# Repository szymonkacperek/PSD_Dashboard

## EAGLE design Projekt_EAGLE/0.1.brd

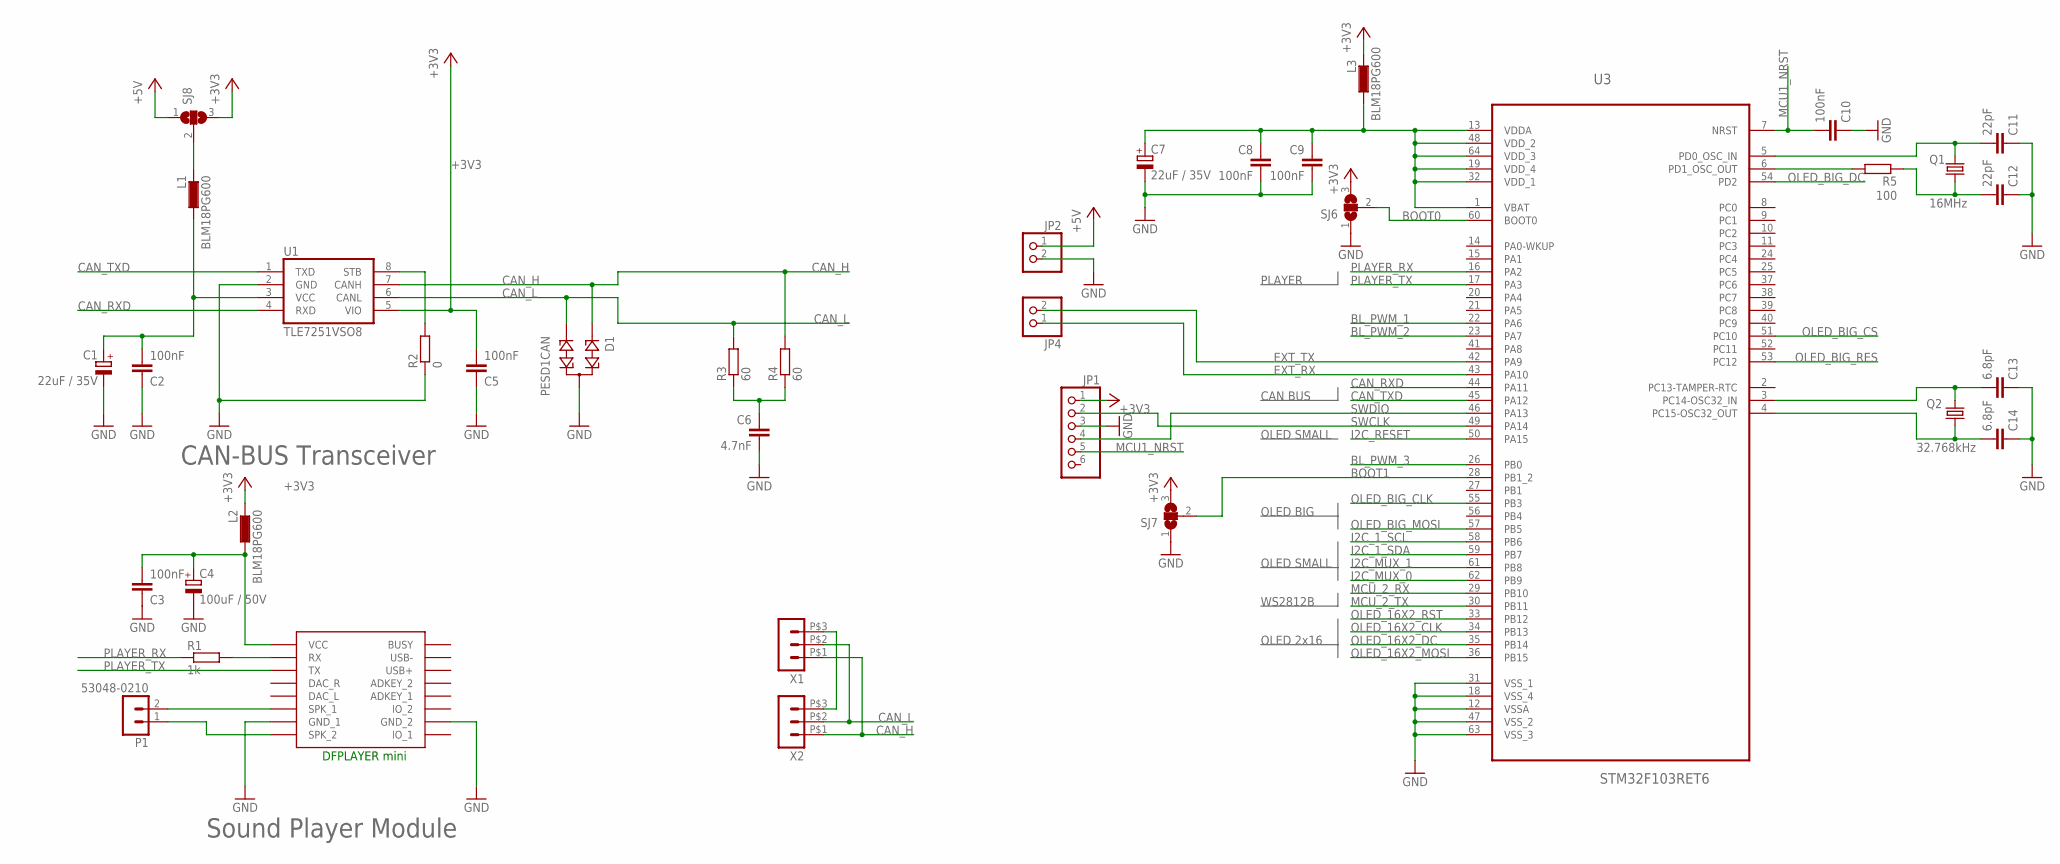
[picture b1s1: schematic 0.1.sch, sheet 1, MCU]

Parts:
C1, C7: 22uF / 35V; SMC_D
C2, C3, C5, C8, C9, C10: 100nF; C0805K
C4: 100uF / 50V; PANASONIC_F
C6: 4.7nF; C0805K
C11, C12: 22pF; C0805K
C13, C14: 6.8pF; C0805K
D1: PESD1CAN; SOT23
JP1: PINHD-1X6; 1X06
JP2, JP4: PINHD-1X2; 1X02
L1, L2, L3: BLM18PG600; L1608
P1: 53048-0210
Q1: 16MHz; SM49
Q2: 32.768kHz; SMD4_270
R1: 1k; R0805
R2: 0; R0805
R3, R4: 60; R0805
R5: 100; R0805
SJ6, SJ7, SJ8: SJ2W; SJ_2
U1: TLE7251VSO8; SO8
U2: DFPLAYER
U3: STM32F103RET6; QFP50P1200X1200X160-64N
X1, X2: HEADER_POS3_43650-0315; 43650-0315

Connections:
+3V3: C5.2, JP1.1, L2.2, L3.2, SJ6.3, SJ7.3, SJ8.3, U1.5 (VIO); also elsewhere on the board
+5V: JP2.1, SJ8.1; also elsewhere on the board
BL_PWM_1: U3.22 (PA6); also elsewhere on the board
BL_PWM_2: U3.23 (PA7); also elsewhere on the board
BL_PWM_3: U3.26 (PB0); also elsewhere on the board
BOOT0: SJ6.2, U3.60 (BOOT0)
BOOT1: SJ7.2, U3.28 (PB1_2)
CAN_H: D1.1, R4.2, U1.7 (CANH), X1.P$1 (1), X2.P$1 (1)
CAN_L: D1.2, R3.2, U1.6 (CANL), X1.P$2 (2), X2.P$2 (2)
CAN_RXD: U1.4 (RXD), U3.44 (PA11)
CAN_STB: R2.2, U1.8 (STB)
CAN_TXD: U1.1 (TXD), U3.45 (PA12)
EXT_RX: JP4.1, U3.43 (PA10)
EXT_TX: JP4.2, U3.42 (PA9)
GND: C1.-, C2.1, C3.1, C4.-, C5.1, C6.2, C7.-, C8.2, C9.2, C10.1, C11.1, C12.1, C13.1, C14.1, D1.3, JP1.3, JP2.2, R2.1, SJ6.1, SJ7.1, U1.2 (GND), U2.GND_1, U2.GND_2, U3.12 (VSSA), U3.18 (VSS_4), U3.31 (VSS_1), U3.47 (VSS_2), U3.63 (VSS_3); also elsewhere on the board
I2C_1_SCL: U3.58 (PB6); also elsewhere on the board
I2C_1_SDA: U3.59 (PB7); also elsewhere on the board
I2C_MUX_0: U3.62 (PB9); also elsewhere on the board
I2C_MUX_1: U3.61 (PB8); also elsewhere on the board
I2C_RESET: U3.50 (PA15); also elsewhere on the board
MCU1_NRST: C10.2, JP1.5, U3.7 (NRST)
MCU_2_RX: U3.29 (PB10); also elsewhere on the board
MCU_2_TX: U3.30 (PB11); also elsewhere on the board
unnamed: R5.2, U3.6 (PD1_OSC_OUT)
unnamed: R1.2, U2.RX
unnamed: C3.2, C4.+, L2.1, U2.VCC
unnamed: X1.P$3 (3), X2.P$3 (3)
unnamed: P1.1, U2.SPK2 (SPK_2)
unnamed: C6.1, R3.1, R4.1
unnamed: C7.+, C8.1, C9.1, L3.1, U3.1 (VBAT), U3.13 (VDDA), U3.19 (VDD_4), U3.32 (VDD_1), U3.48 (VDD_2), U3.64 (VDD_3)
unnamed: P1.2, U2.SPK1 (SPK_1)
unnamed: L1.2, SJ8.2
unnamed: C11.2, Q1.1, U3.5 (PD0_OSC_IN)
unnamed: C12.2, Q1.2, R5.1
unnamed: C13.2, Q2.4 (2), U3.3 (PC14-OSC32_IN)
unnamed: C14.2, Q2.1, U3.4 (PC15-OSC32_OUT)
unnamed: C1.+, C2.2, L1.1, U1.3 (VCC)
OLED_16X2_CLK: U3.34 (PB13); also elsewhere on the board
OLED_16X2_DC: U3.35 (PB14); also elsewhere on the board
OLED_16X2_MOSI: U3.36 (PB15); also elsewhere on the board
OLED_16X2_RST: U3.33 (PB12); also elsewhere on the board
OLED_BIG_CLK: U3.55 (PB3); also elsewhere on the board
OLED_BIG_CS: U3.51 (PC10); also elsewhere on the board
OLED_BIG_DC: U3.54 (PD2); also elsewhere on the board
OLED_BIG_MOSI: U3.57 (PB5); also elsewhere on the board
OLED_BIG_RES: U3.53 (PC12); also elsewhere on the board
PLAYER_RX: R1.1, U3.16 (PA2)
PLAYER_TX: U2.TX, U3.17 (PA3)
SWCLK: JP1.2, U3.49 (PA14)
SWDIO: JP1.4, U3.46 (PA13)

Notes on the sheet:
CAN-BUS Transceiver
Sound Player Module
OLED 2x16
OLED BIG
OLED SMALL
PLAYER
WS2812B
CAN BUS
DFPLAYER mini

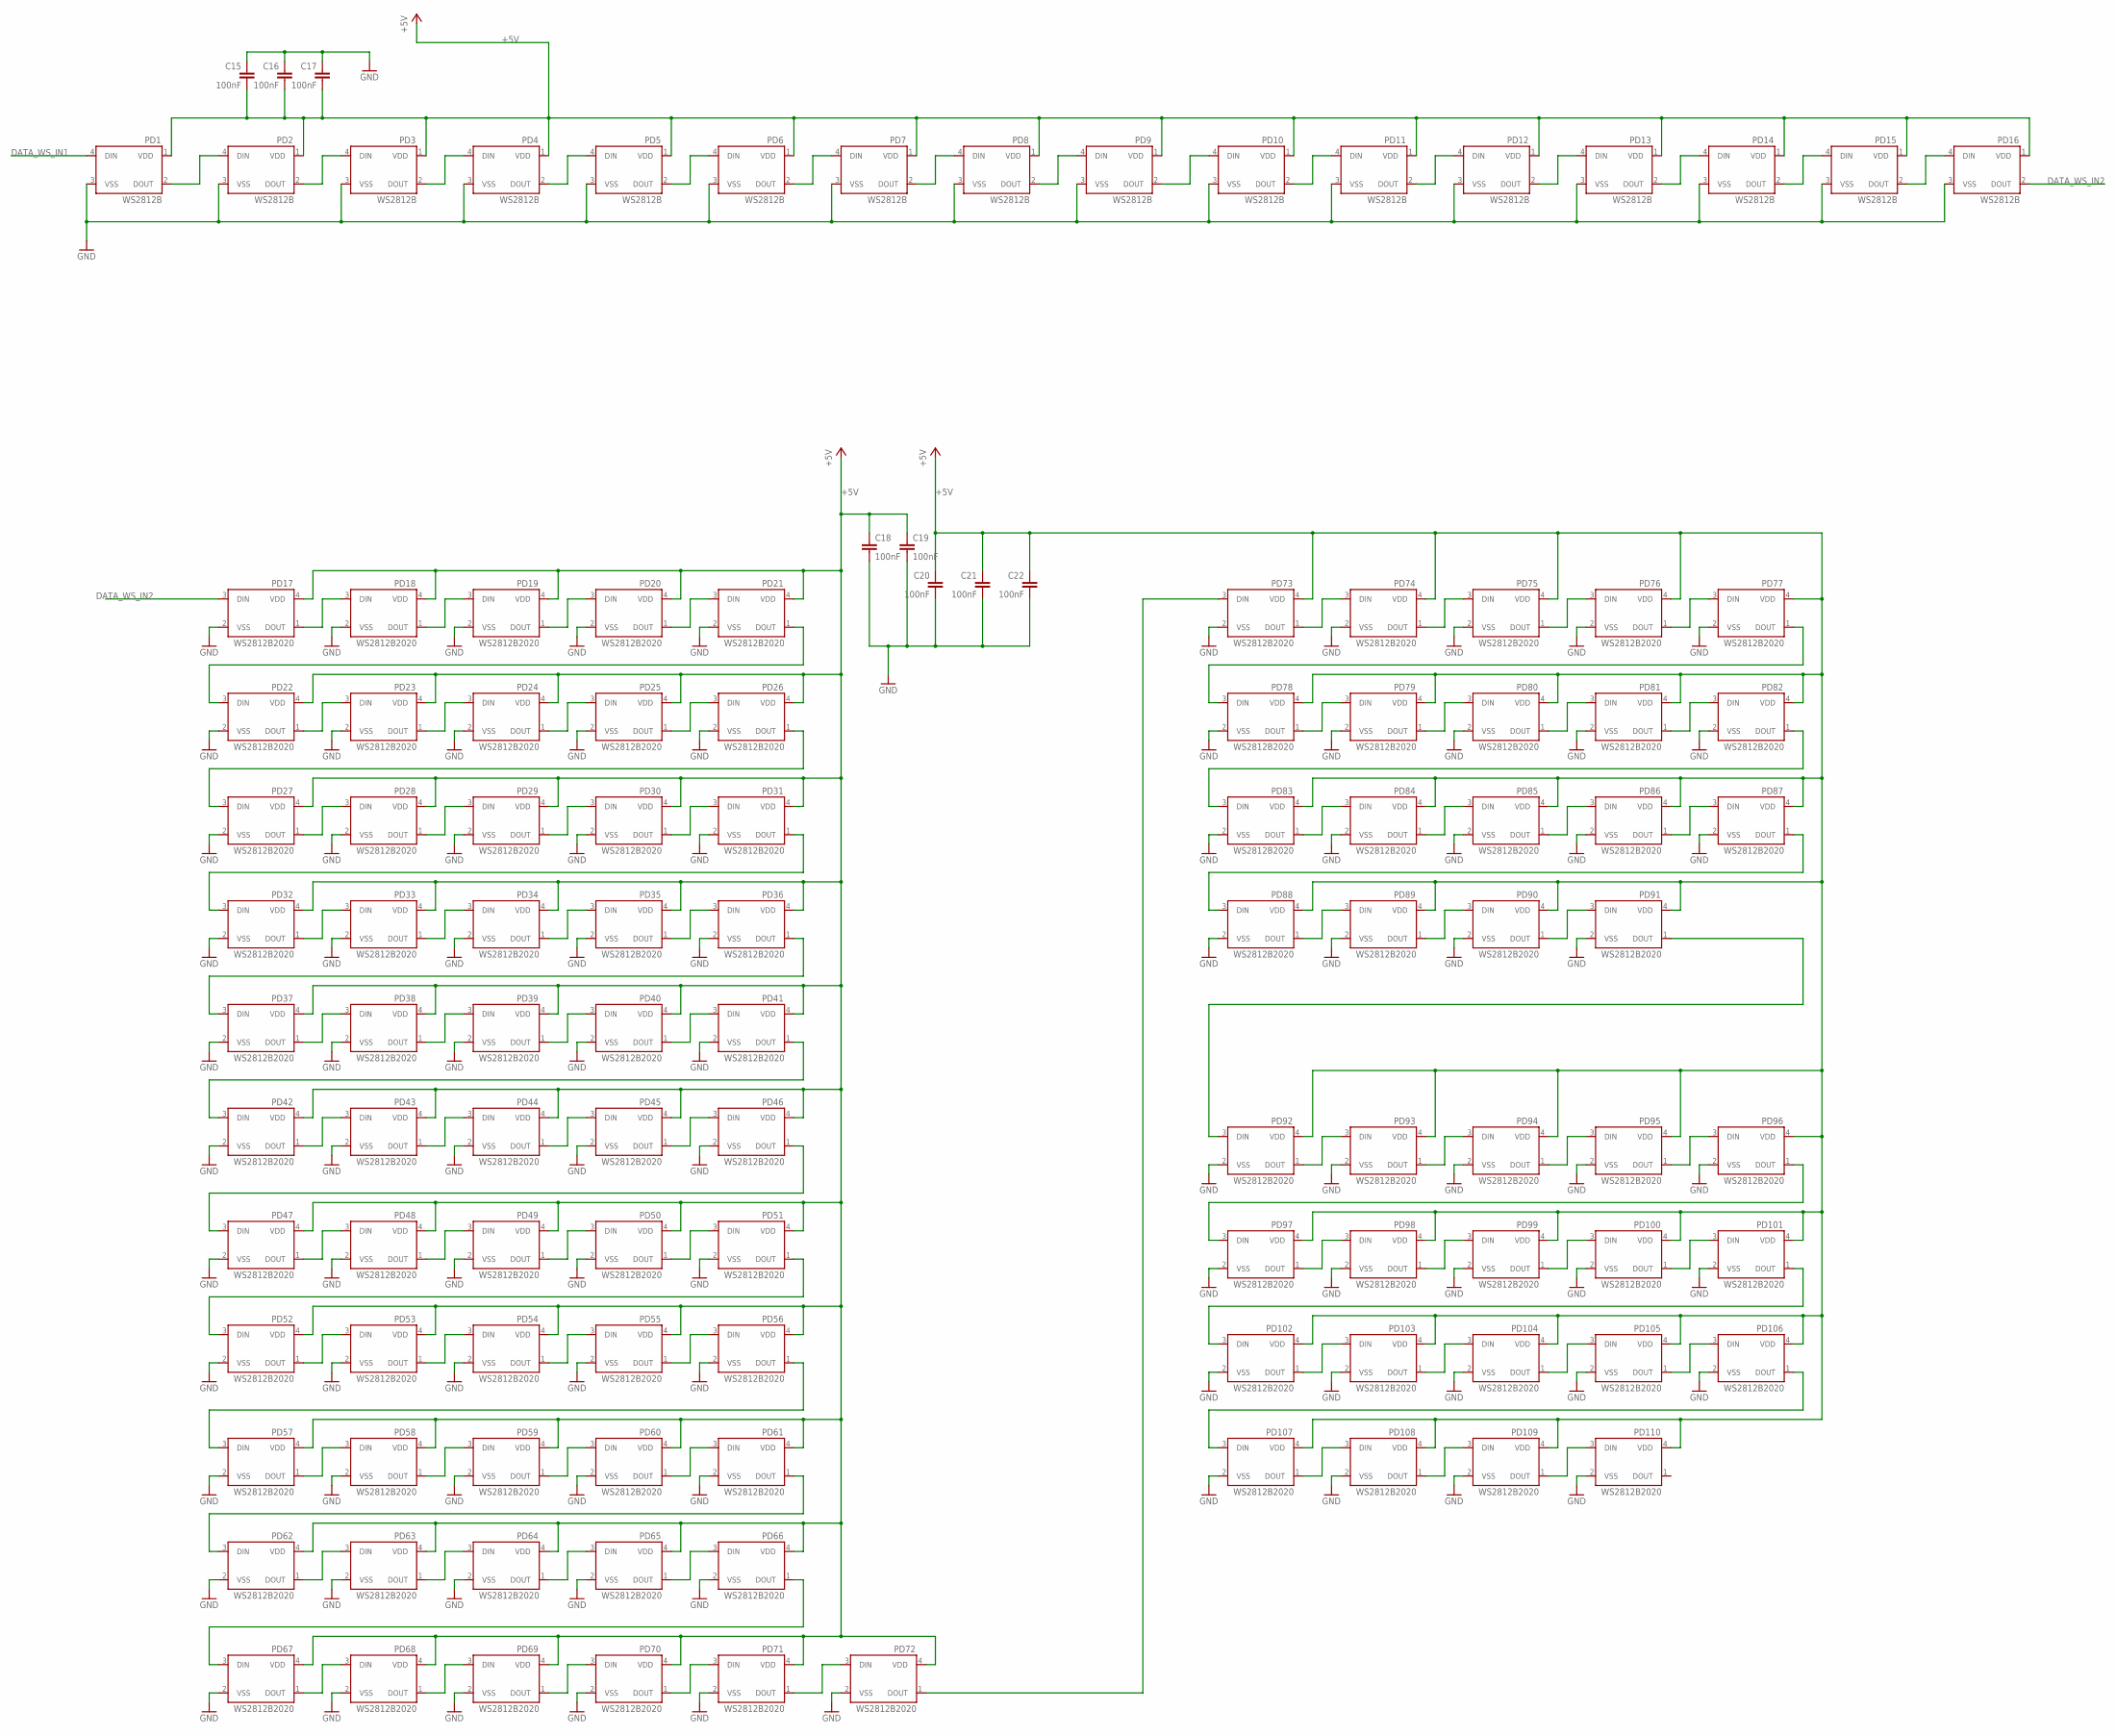
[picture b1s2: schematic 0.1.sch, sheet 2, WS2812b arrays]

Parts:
C15, C16, C17, C18, C19, C20, C21, C22: 100nF; C0805K
PD1, PD2, PD3, PD4, PD5, PD6, PD7, PD8, PD9, PD10, PD11, PD12, PD13, PD14, PD15, PD16: WS2812B; 5050
PD17, PD18, PD19, PD20, PD21, PD22, PD23, PD24, PD25, PD26, PD27, PD28, PD29, PD30, PD31, PD32, PD33, PD34, PD35, PD36, PD37, PD38, PD39, PD40, PD41, PD42, PD43, PD44, PD45, PD46, PD47, PD48, PD49, PD50, PD51, PD52, PD53, PD54, PD55, PD56, PD57, PD58, PD59, PD60, PD61, PD62, PD63, PD64, PD65, PD66, PD67, PD68, PD69, PD70, PD71, PD72, PD73, PD74, PD75, PD76, PD77, PD78, PD79, PD80, PD81, PD82, PD83, PD84, PD85, PD86, PD87, PD88, PD89, PD90, PD91, PD92, PD93, PD94, PD95, PD96, PD97, PD98, PD99, PD100, PD101, PD102, PD103, PD104, PD105, PD106, PD107, PD108, PD109, PD110: WS2812B2020; LED_WS2812-2020

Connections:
+5V: C15.2, C16.2, C17.2, C18.1, C19.1, C20.1, C21.1, C22.1, PD1.1 (VDD), PD2.1 (VDD), PD3.1 (VDD), PD4.1 (VDD), PD5.1 (VDD), PD6.1 (VDD), PD7.1 (VDD), PD8.1 (VDD), PD9.1 (VDD), PD10.1 (VDD), PD11.1 (VDD), PD12.1 (VDD), PD13.1 (VDD), PD14.1 (VDD), PD15.1 (VDD), PD16.1 (VDD), PD17.4 (VDD), PD18.4 (VDD), PD19.4 (VDD), PD20.4 (VDD), PD21.4 (VDD), PD22.4 (VDD), PD23.4 (VDD), PD24.4 (VDD), PD25.4 (VDD), PD26.4 (VDD), PD27.4 (VDD), PD28.4 (VDD), PD29.4 (VDD), PD30.4 (VDD), PD31.4 (VDD), PD32.4 (VDD), PD33.4 (VDD), PD34.4 (VDD), PD35.4 (VDD), PD36.4 (VDD), PD37.4 (VDD), PD38.4 (VDD), PD39.4 (VDD), PD40.4 (VDD), PD41.4 (VDD), PD42.4 (VDD), PD43.4 (VDD), PD44.4 (VDD), PD45.4 (VDD), PD46.4 (VDD), PD47.4 (VDD), PD48.4 (VDD), PD49.4 (VDD), PD50.4 (VDD), PD51.4 (VDD), PD52.4 (VDD), PD53.4 (VDD), PD54.4 (VDD), PD55.4 (VDD), PD56.4 (VDD), PD57.4 (VDD), PD58.4 (VDD), PD59.4 (VDD), PD60.4 (VDD), PD61.4 (VDD), PD62.4 (VDD), PD63.4 (VDD), PD64.4 (VDD), PD65.4 (VDD), PD66.4 (VDD), PD67.4 (VDD), PD68.4 (VDD), PD69.4 (VDD), PD70.4 (VDD), PD71.4 (VDD), PD72.4 (VDD), PD73.4 (VDD), PD74.4 (VDD), PD75.4 (VDD), PD76.4 (VDD), PD77.4 (VDD), PD78.4 (VDD), PD79.4 (VDD), PD80.4 (VDD), PD81.4 (VDD), PD82.4 (VDD), PD83.4 (VDD), PD84.4 (VDD), PD85.4 (VDD), PD86.4 (VDD), PD87.4 (VDD), PD88.4 (VDD), PD89.4 (VDD), PD90.4 (VDD), PD91.4 (VDD), PD92.4 (VDD), PD93.4 (VDD), PD94.4 (VDD), PD95.4 (VDD), PD96.4 (VDD), PD97.4 (VDD), PD98.4 (VDD), PD99.4 (VDD), PD100.4 (VDD), PD101.4 (VDD), PD102.4 (VDD), PD103.4 (VDD), PD104.4 (VDD), PD105.4 (VDD), PD106.4 (VDD), PD107.4 (VDD), PD108.4 (VDD), PD109.4 (VDD), PD110.4 (VDD); also elsewhere on the board
DATA_WS_IN1: PD1.4 (DIN); also elsewhere on the board
DATA_WS_IN2: PD16.2 (DOUT), PD17.3 (DIN)
DATA_WS_IN3: PD72.1 (DOUT), PD73.3 (DIN)
GND: C15.1, C16.1, C17.1, C18.2, C19.2, C20.2, C21.2, C22.2, PD1.3 (VSS), PD2.3 (VSS), PD3.3 (VSS), PD4.3 (VSS), PD5.3 (VSS), PD6.3 (VSS), PD7.3 (VSS), PD8.3 (VSS), PD9.3 (VSS), PD10.3 (VSS), PD11.3 (VSS), PD12.3 (VSS), PD13.3 (VSS), PD14.3 (VSS), PD15.3 (VSS), PD16.3 (VSS), PD17.2 (VSS), PD18.2 (VSS), PD19.2 (VSS), PD20.2 (VSS), PD21.2 (VSS), PD22.2 (VSS), PD23.2 (VSS), PD24.2 (VSS), PD25.2 (VSS), PD26.2 (VSS), PD27.2 (VSS), PD28.2 (VSS), PD29.2 (VSS), PD30.2 (VSS), PD31.2 (VSS), PD32.2 (VSS), PD33.2 (VSS), PD34.2 (VSS), PD35.2 (VSS), PD36.2 (VSS), PD37.2 (VSS), PD38.2 (VSS), PD39.2 (VSS), PD40.2 (VSS), PD41.2 (VSS), PD42.2 (VSS), PD43.2 (VSS), PD44.2 (VSS), PD45.2 (VSS), PD46.2 (VSS), PD47.2 (VSS), PD48.2 (VSS), PD49.2 (VSS), PD50.2 (VSS), PD51.2 (VSS), PD52.2 (VSS), PD53.2 (VSS), PD54.2 (VSS), PD55.2 (VSS), PD56.2 (VSS), PD57.2 (VSS), PD58.2 (VSS), PD59.2 (VSS), PD60.2 (VSS), PD61.2 (VSS), PD62.2 (VSS), PD63.2 (VSS), PD64.2 (VSS), PD65.2 (VSS), PD66.2 (VSS), PD67.2 (VSS), PD68.2 (VSS), PD69.2 (VSS), PD70.2 (VSS), PD71.2 (VSS), PD72.2 (VSS), PD73.2 (VSS), PD74.2 (VSS), PD75.2 (VSS), PD76.2 (VSS), PD77.2 (VSS), PD78.2 (VSS), PD79.2 (VSS), PD80.2 (VSS), PD81.2 (VSS), PD82.2 (VSS), PD83.2 (VSS), PD84.2 (VSS), PD85.2 (VSS), PD86.2 (VSS), PD87.2 (VSS), PD88.2 (VSS), PD89.2 (VSS), PD90.2 (VSS), PD91.2 (VSS), PD92.2 (VSS), PD93.2 (VSS), PD94.2 (VSS), PD95.2 (VSS), PD96.2 (VSS), PD97.2 (VSS), PD98.2 (VSS), PD99.2 (VSS), PD100.2 (VSS), PD101.2 (VSS), PD102.2 (VSS), PD103.2 (VSS), PD104.2 (VSS), PD105.2 (VSS), PD106.2 (VSS), PD107.2 (VSS), PD108.2 (VSS), PD109.2 (VSS), PD110.2 (VSS); also elsewhere on the board
unnamed: PD1.2 (DOUT), PD2.4 (DIN)
unnamed: PD2.2 (DOUT), PD3.4 (DIN)
unnamed: PD3.2 (DOUT), PD4.4 (DIN)
unnamed: PD4.2 (DOUT), PD5.4 (DIN)
unnamed: PD5.2 (DOUT), PD6.4 (DIN)
unnamed: PD6.2 (DOUT), PD7.4 (DIN)
unnamed: PD7.2 (DOUT), PD8.4 (DIN)
unnamed: PD9.2 (DOUT), PD10.4 (DIN)
unnamed: PD10.2 (DOUT), PD11.4 (DIN)
unnamed: PD11.2 (DOUT), PD12.4 (DIN)
unnamed: PD12.2 (DOUT), PD13.4 (DIN)
unnamed: PD13.2 (DOUT), PD14.4 (DIN)
unnamed: PD14.2 (DOUT), PD15.4 (DIN)
unnamed: PD15.2 (DOUT), PD16.4 (DIN)
unnamed: PD8.2 (DOUT), PD9.4 (DIN)
unnamed: PD21.1 (DOUT), PD22.3 (DIN)
unnamed: PD17.1 (DOUT), PD18.3 (DIN)
unnamed: PD18.1 (DOUT), PD19.3 (DIN)
unnamed: PD19.1 (DOUT), PD20.3 (DIN)
unnamed: PD20.1 (DOUT), PD21.3 (DIN)
unnamed: PD22.1 (DOUT), PD23.3 (DIN)
unnamed: PD23.1 (DOUT), PD24.3 (DIN)
unnamed: PD24.1 (DOUT), PD25.3 (DIN)
unnamed: PD25.1 (DOUT), PD26.3 (DIN)
unnamed: PD26.1 (DOUT), PD27.3 (DIN)
unnamed: PD27.1 (DOUT), PD28.3 (DIN)
unnamed: PD28.1 (DOUT), PD29.3 (DIN)
unnamed: PD29.1 (DOUT), PD30.3 (DIN)
unnamed: PD30.1 (DOUT), PD31.3 (DIN)
unnamed: PD31.1 (DOUT), PD32.3 (DIN)
unnamed: PD32.1 (DOUT), PD33.3 (DIN)
unnamed: PD33.1 (DOUT), PD34.3 (DIN)
unnamed: PD34.1 (DOUT), PD35.3 (DIN)
unnamed: PD35.1 (DOUT), PD36.3 (DIN)
unnamed: PD36.1 (DOUT), PD37.3 (DIN)
unnamed: PD37.1 (DOUT), PD38.3 (DIN)
unnamed: PD38.1 (DOUT), PD39.3 (DIN)
unnamed: PD39.1 (DOUT), PD40.3 (DIN)
unnamed: PD40.1 (DOUT), PD41.3 (DIN)
unnamed: PD41.1 (DOUT), PD42.3 (DIN)
unnamed: PD42.1 (DOUT), PD43.3 (DIN)
unnamed: PD43.1 (DOUT), PD44.3 (DIN)
unnamed: PD44.1 (DOUT), PD45.3 (DIN)
unnamed: PD45.1 (DOUT), PD46.3 (DIN)
unnamed: PD46.1 (DOUT), PD47.3 (DIN)
unnamed: PD47.1 (DOUT), PD48.3 (DIN)
unnamed: PD48.1 (DOUT), PD49.3 (DIN)
unnamed: PD49.1 (DOUT), PD50.3 (DIN)
unnamed: PD50.1 (DOUT), PD51.3 (DIN)
unnamed: PD51.1 (DOUT), PD52.3 (DIN)
unnamed: PD52.1 (DOUT), PD53.3 (DIN)
unnamed: PD53.1 (DOUT), PD54.3 (DIN)
unnamed: PD54.1 (DOUT), PD55.3 (DIN)
unnamed: PD55.1 (DOUT), PD56.3 (DIN)
unnamed: PD56.1 (DOUT), PD57.3 (DIN)
unnamed: PD57.1 (DOUT), PD58.3 (DIN)
unnamed: PD58.1 (DOUT), PD59.3 (DIN)
unnamed: PD59.1 (DOUT), PD60.3 (DIN)
unnamed: PD60.1 (DOUT), PD61.3 (DIN)
unnamed: PD61.1 (DOUT), PD62.3 (DIN)
unnamed: PD62.1 (DOUT), PD63.3 (DIN)
unnamed: PD63.1 (DOUT), PD64.3 (DIN)
unnamed: PD64.1 (DOUT), PD65.3 (DIN)
unnamed: PD65.1 (DOUT), PD66.3 (DIN)
unnamed: PD66.1 (DOUT), PD67.3 (DIN)
unnamed: PD92.1 (DOUT), PD93.3 (DIN)
unnamed: PD67.1 (DOUT), PD68.3 (DIN)
unnamed: PD68.1 (DOUT), PD69.3 (DIN)
unnamed: PD69.1 (DOUT), PD70.3 (DIN)
unnamed: PD70.1 (DOUT), PD71.3 (DIN)
unnamed: PD71.1 (DOUT), PD72.3 (DIN)
unnamed: PD93.1 (DOUT), PD94.3 (DIN)
unnamed: PD94.1 (DOUT), PD95.3 (DIN)
unnamed: PD95.1 (DOUT), PD96.3 (DIN)
unnamed: PD73.1 (DOUT), PD74.3 (DIN)
unnamed: PD74.1 (DOUT), PD75.3 (DIN)
unnamed: PD75.1 (DOUT), PD76.3 (DIN)
unnamed: PD76.1 (DOUT), PD77.3 (DIN)
unnamed: PD77.1 (DOUT), PD78.3 (DIN)
unnamed: PD78.1 (DOUT), PD79.3 (DIN)
unnamed: PD79.1 (DOUT), PD80.3 (DIN)
unnamed: PD80.1 (DOUT), PD81.3 (DIN)
unnamed: PD81.1 (DOUT), PD82.3 (DIN)
unnamed: PD82.1 (DOUT), PD83.3 (DIN)
unnamed: PD83.1 (DOUT), PD84.3 (DIN)
unnamed: PD84.1 (DOUT), PD85.3 (DIN)
unnamed: PD85.1 (DOUT), PD86.3 (DIN)
unnamed: PD86.1 (DOUT), PD87.3 (DIN)
unnamed: PD87.1 (DOUT), PD88.3 (DIN)
unnamed: PD88.1 (DOUT), PD89.3 (DIN)
unnamed: PD89.1 (DOUT), PD90.3 (DIN)
unnamed: PD90.1 (DOUT), PD91.3 (DIN)
unnamed: PD91.1 (DOUT), PD92.3 (DIN)
unnamed: PD96.1 (DOUT), PD97.3 (DIN)
unnamed: PD97.1 (DOUT), PD98.3 (DIN)
unnamed: PD98.1 (DOUT), PD99.3 (DIN)
unnamed: PD99.1 (DOUT), PD100.3 (DIN)
unnamed: PD100.1 (DOUT), PD101.3 (DIN)
unnamed: PD101.1 (DOUT), PD102.3 (DIN)
unnamed: PD102.1 (DOUT), PD103.3 (DIN)
unnamed: PD103.1 (DOUT), PD104.3 (DIN)
unnamed: PD104.1 (DOUT), PD105.3 (DIN)
unnamed: PD105.1 (DOUT), PD106.3 (DIN)
unnamed: PD106.1 (DOUT), PD107.3 (DIN)
unnamed: PD107.1 (DOUT), PD108.3 (DIN)
unnamed: PD108.1 (DOUT), PD109.3 (DIN)
unnamed: PD109.1 (DOUT), PD110.3 (DIN)

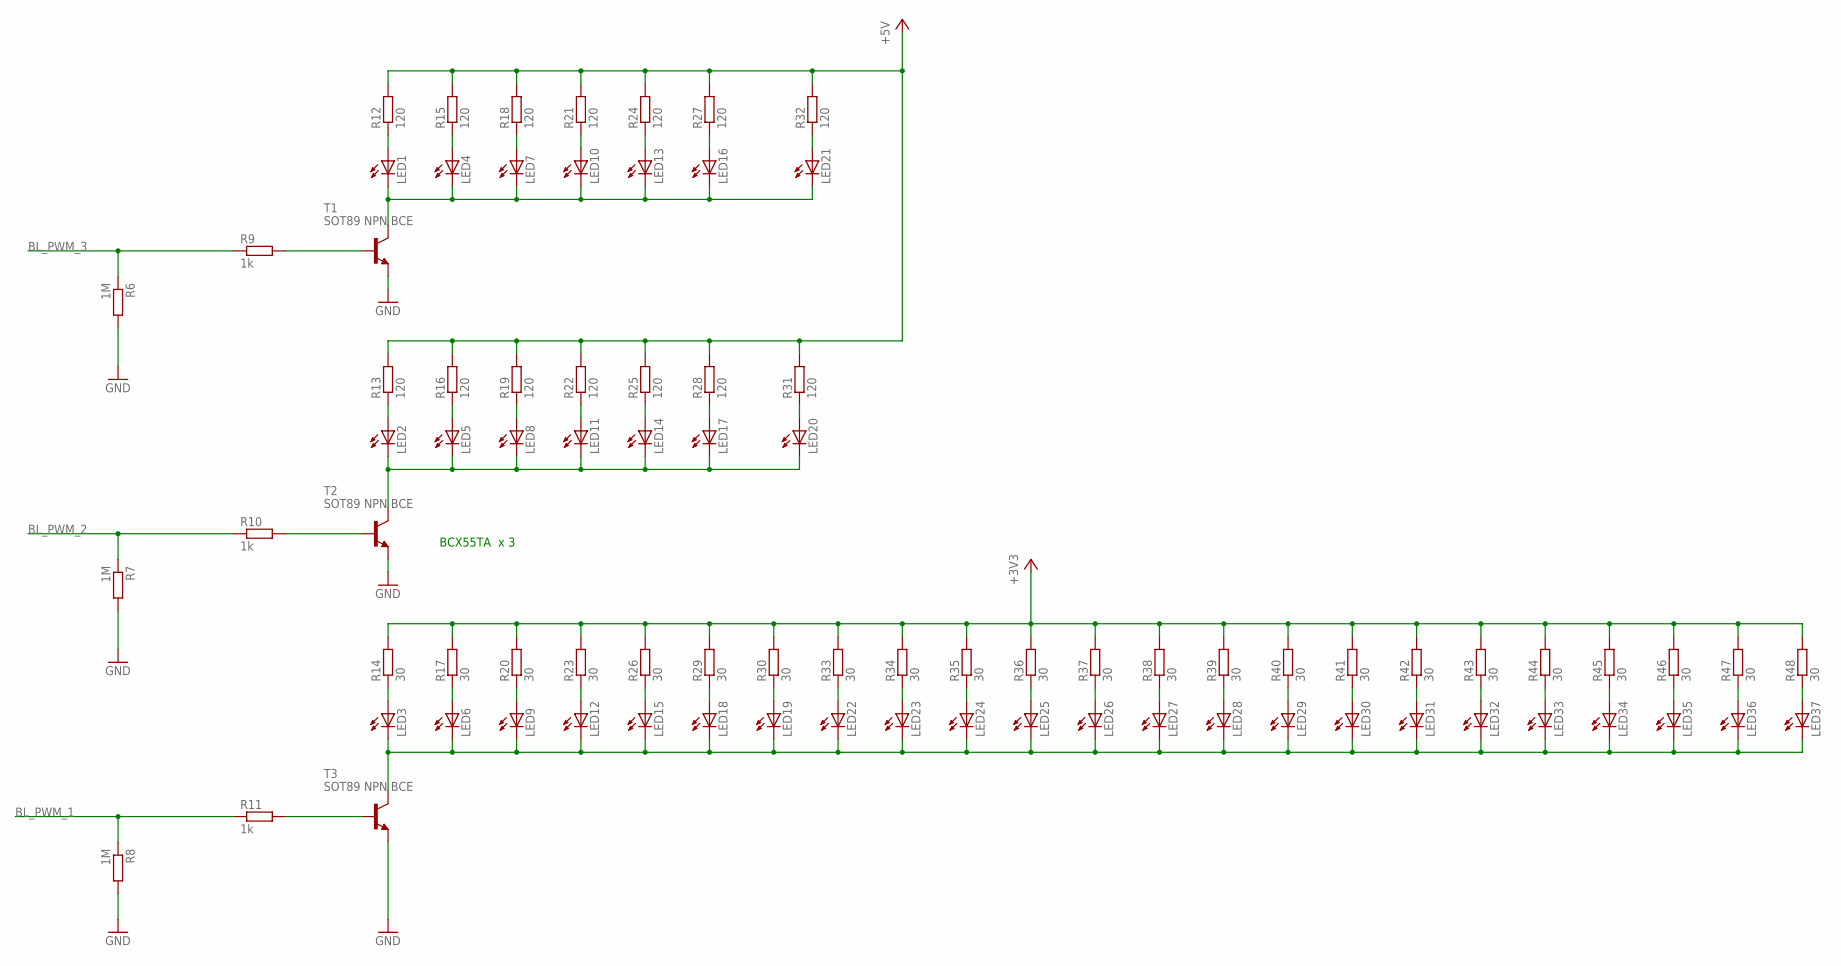
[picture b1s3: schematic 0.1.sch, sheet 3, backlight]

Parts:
LED1, LED2, LED3, LED4, LED5, LED6, LED7, LED8, LED9, LED10, LED11, LED12, LED13, LED14, LED15, LED16, LED17, LED18, LED19, LED20, LED21, LED22, LED23, LED24, LED25, LED26, LED27, LED28, LED29, LED30, LED31, LED32, LED33, LED34, LED35, LED36, LED37: LEDCHIPLED_0603; CHIPLED_0603
R6, R7, R8: 1M; R0805
R9, R10, R11: 1k; R0805
R12, R13, R15, R16, R18, R19, R21, R22, R24, R25, R27, R28, R31, R32: 120; R0805
R14, R17, R20, R23, R26, R29, R30, R33, R34, R35, R36, R37, R38, R39, R40, R41, R42, R43, R44, R45, R46, R47, R48: 30; R0805
T1, T2, T3: SOT89 NPN BCE; SOT89-BCE

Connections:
+3V3: R14.2, R17.2, R20.2, R23.2, R26.2, R29.2, R30.2, R33.2, R34.2, R35.2, R36.2, R37.2, R38.2, R39.2, R40.2, R41.2, R42.2, R43.2, R44.2, R45.2, R46.2, R47.2, R48.2; also elsewhere on the board
+5V: R12.2, R13.2, R15.2, R16.2, R18.2, R19.2, R21.2, R22.2, R24.2, R25.2, R27.2, R28.2, R31.2, R32.2; also elsewhere on the board
BL_PWM_1: R8.1, R11.1; also elsewhere on the board
BL_PWM_2: R7.1, R10.1; also elsewhere on the board
BL_PWM_3: R6.1, R9.1; also elsewhere on the board
GND: R6.2, R7.2, R8.2, T1.E, T2.E, T3.E; also elsewhere on the board
unnamed: LED1.C, LED4.C, LED7.C, LED10.C, LED13.C, LED16.C, LED21.C, T1.C
unnamed: LED2.C, LED5.C, LED8.C, LED11.C, LED14.C, LED17.C, LED20.C, T2.C
unnamed: R9.2, T1.B
unnamed: R10.2, T2.B
unnamed: R11.2, T3.B
unnamed: LED1.A, R12.1
unnamed: LED4.A, R15.1
unnamed: LED7.A, R18.1
unnamed: LED10.A, R21.1
unnamed: LED13.A, R24.1
unnamed: LED16.A, R27.1
unnamed: LED23.A, R34.1
unnamed: LED24.A, R35.1
unnamed: LED25.A, R36.1
unnamed: LED26.A, R37.1
unnamed: LED27.A, R38.1
unnamed: LED28.A, R39.1
unnamed: LED29.A, R40.1
unnamed: LED3.C, LED6.C, LED9.C, LED12.C, LED15.C, LED18.C, LED19.C, LED22.C, LED23.C, LED24.C, LED25.C, LED26.C, LED27.C, LED28.C, LED29.C, LED30.C, LED31.C, LED32.C, LED33.C, LED34.C, LED35.C, LED36.C, LED37.C, T3.C
unnamed: LED3.A, R14.1
unnamed: LED2.A, R13.1
unnamed: LED5.A, R16.1
unnamed: LED8.A, R19.1
unnamed: LED11.A, R22.1
unnamed: LED14.A, R25.1
unnamed: LED17.A, R28.1
unnamed: LED30.A, R41.1
unnamed: LED21.A, R32.1
unnamed: LED20.A, R31.1
unnamed: LED6.A, R17.1
unnamed: LED9.A, R20.1
unnamed: LED12.A, R23.1
unnamed: LED31.A, R42.1
unnamed: LED15.A, R26.1
unnamed: LED18.A, R29.1
unnamed: LED19.A, R30.1
unnamed: LED22.A, R33.1
unnamed: LED32.A, R43.1
unnamed: LED33.A, R44.1
unnamed: LED34.A, R45.1
unnamed: LED35.A, R46.1
unnamed: LED36.A, R47.1
unnamed: LED37.A, R48.1

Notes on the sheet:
BCX55TA x 3

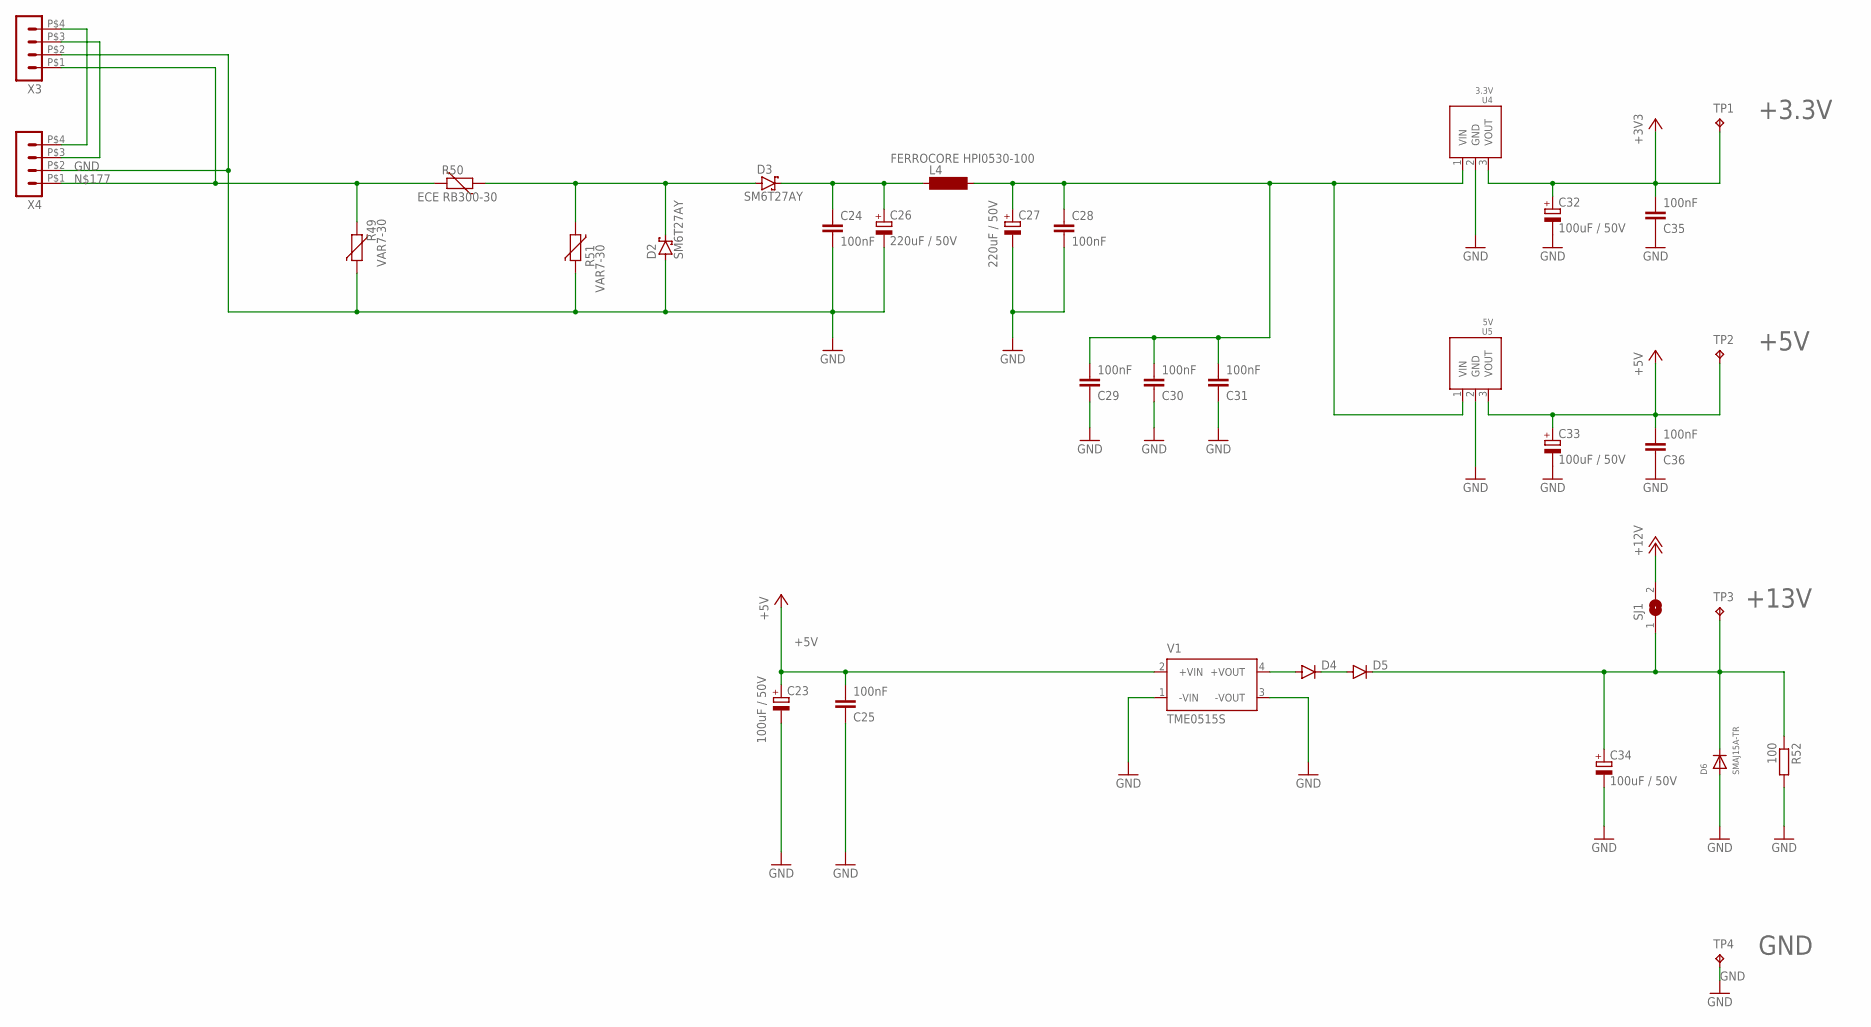
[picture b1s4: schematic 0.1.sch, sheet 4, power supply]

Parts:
C23, C32, C33, C34: 100uF / 50V; PANASONIC_F
C24, C28: 100nF; C1206K
C25, C29, C30, C31, C35, C36: 100nF; C0805K
C26, C27: 220uF / 50V; PANASONIC_G
D2, D3: SM6T27AY; SMB
D4, D5: DIODE-SOD123; SOD123
D6: SMAJ15A-TR; SMADIODE
L4: FERROCORE HPI0530-100; MS85
R49, R51: VAR7-30; S07K11
R50: ECE RB300-30; S07K11
R52: 100; R0805
SJ1: SJ
TP1: 3V3; TP18SQ
TP2: 5V; TP18SQ
TP3: 12V; TP18SQ
TP4: GND; TP18SQ
U4: 3.3V; FDSM-173XXXX42
U5: 5V; FDSM-173XXXX42
V1: TME0515S; TME
X3, X4: HEADER_POS4_43045-0412; 43045-0412

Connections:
+3V3: C32.+, C35.2, TP1.TP, U4.3 (VOUT); also elsewhere on the board
+5V: C23.+, C25.2, C33.+, C36.2, TP2.TP, U5.3 (VOUT), V1.2 (+VIN); also elsewhere on the board
+12V: SJ1.2; also elsewhere on the board
GND: C23.-, C24.2, C25.1, C26.-, C27.-, C28.2, C29.1, C30.1, C31.1, C32.-, C33.-, C34.-, C35.1, C36.1, D2.A, D6.A, R49.2, R51.2, R52.2, TP4.TP, U4.2 (GND), U5.2 (GND), V1.1 (-VIN), V1.3 (-VOUT), X3.P$2 (2), X4.P$2 (2); also elsewhere on the board
unnamed: C27.+, C28.1, C29.2, C30.2, C31.2, L4.2, U4.1 (VIN), U5.1 (VIN)
unnamed: D2.C, D3.A, R50.1, R51.1
unnamed: D4.A, V1.4 (+VOUT)
unnamed: D4.C, D5.A
unnamed: C24.1, C26.+, D3.C, L4.1
unnamed: C34.+, D5.C, D6.C, R52.1, SJ1.1, TP3.TP
unnamed: X3.P$4 (4), X4.P$4 (4)
unnamed: X3.P$3 (3), X4.P$3 (3)
unnamed: R49.1, R50.2, X3.P$1 (1), X4.P$1 (1)

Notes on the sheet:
+3.3V
+5V
GND
+13V

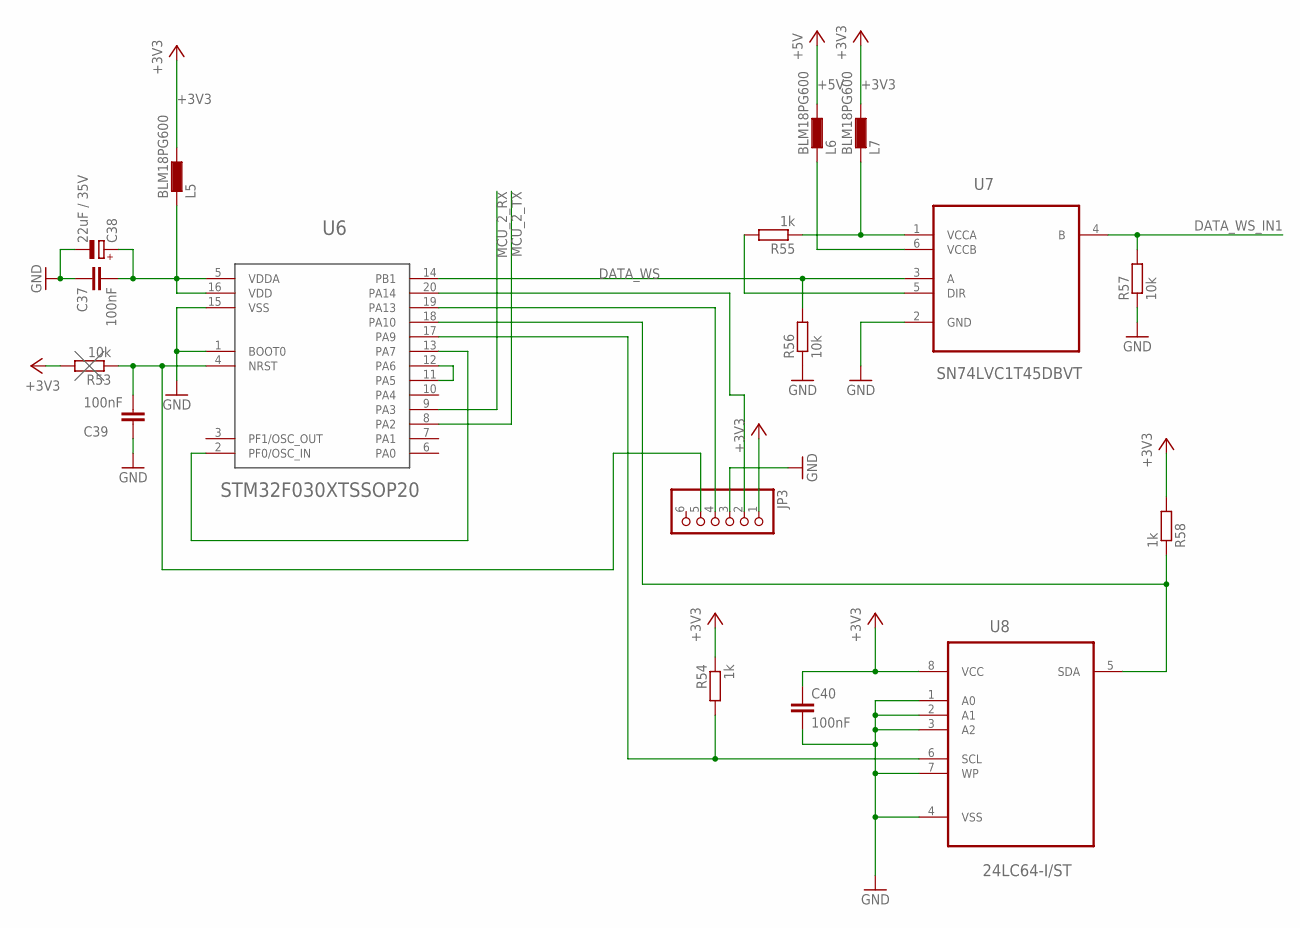
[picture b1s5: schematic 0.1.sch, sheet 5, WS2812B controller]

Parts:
C37, C39, C40: 100nF; C0805K
C38: 22uF / 35V; SMC_D
JP3: PINHD-1X6; 1X06
L5, L6, L7: BLM18PG600; L1608
R53, R56, R57: 10k; R0805
R54, R55, R58: 1k; R0805
U6: STM32F030XTSSOP20; TSSOP-20
U7: SN74LVC1T45DBVT; SOT95P280X145-6N
U8: 24LC64-I/ST; SOP65P638X110-8N

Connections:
+3V3: C40.1, JP3.1, L5.1, L7.1, R53.2, R54.1, R58.2, U8.8 (VCC); also elsewhere on the board
+5V: L6.1; also elsewhere on the board
DATA_WS: R56.2, U6.14 (PB1), U7.3 (A)
DATA_WS_IN1: R57.2, U7.4 (B); also elsewhere on the board
GND: C37.1, C38.-, C39.1, C40.2, JP3.3, R56.1, R57.1, U6.1 (BOOT0), U6.15 (VSS), U7.2 (GND), U8.1 (A0), U8.2 (A1), U8.3 (A2), U8.4 (VSS), U8.7 (WP); also elsewhere on the board
MCU_2_RX: U6.9 (PA3); also elsewhere on the board
MCU_2_TX: U6.8 (PA2); also elsewhere on the board
unnamed: R55.2, U7.5 (DIR)
unnamed: L7.2, R55.1, U7.1 (VCCA)
unnamed: L6.2, U7.6 (VCCB)
unnamed: C39.2, JP3.5, R53.1, U6.4 (NRST)
unnamed: U6.2 (PF0/OSC_IN), U6.13 (PA7)
unnamed: U6.11 (PA5), U6.12 (PA6)
unnamed: JP3.4, U6.19 (PA13)
unnamed: JP3.2, U6.20 (PA14)
unnamed: R58.1, U6.18 (PA10), U8.5 (SDA)
unnamed: R54.2, U6.17 (PA9), U8.6 (SCL)
unnamed: C37.2, C38.+, L5.2, U6.5 (VDDA), U6.16 (VDD)

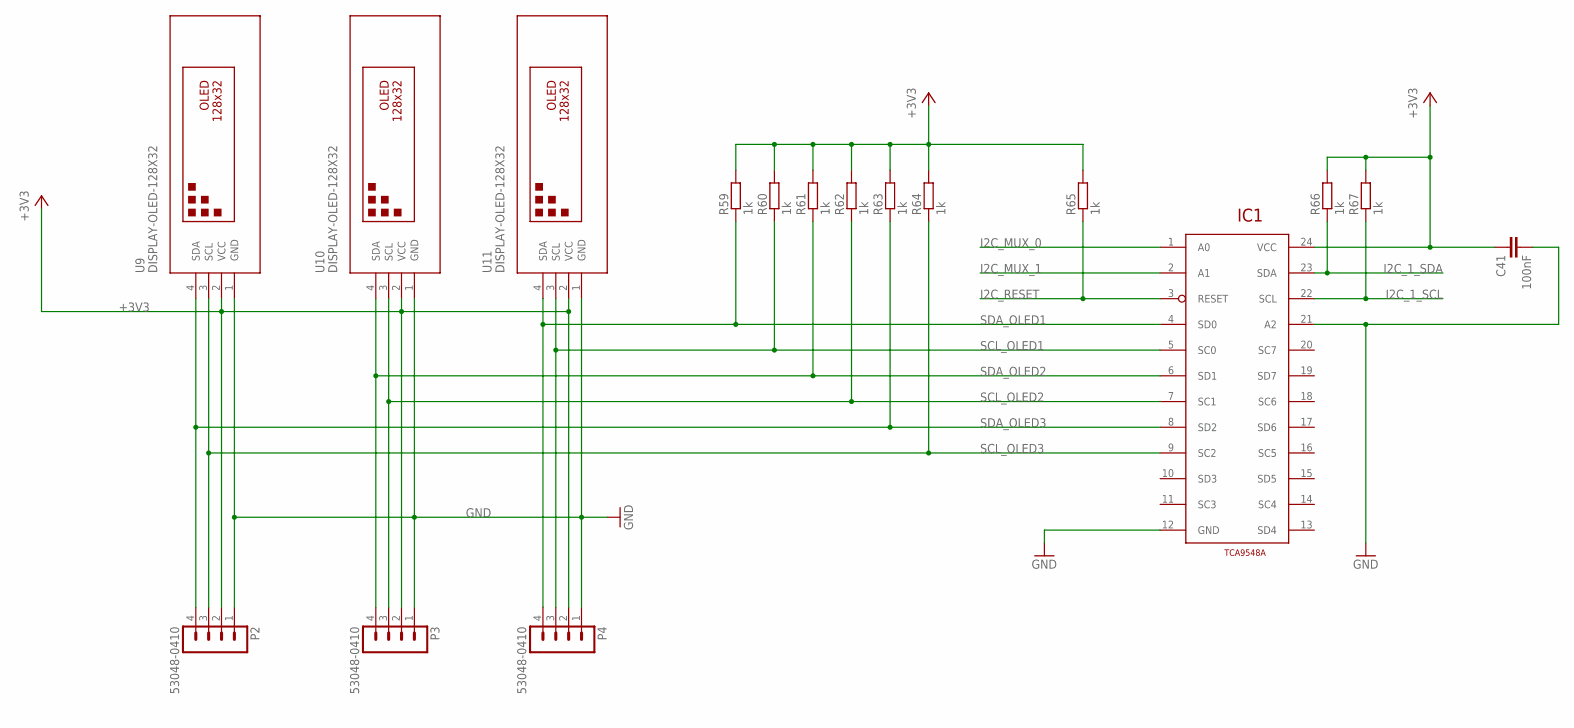
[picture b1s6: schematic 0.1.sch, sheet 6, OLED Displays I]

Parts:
C41: 100nF; C0805K
IC1: TCA9548A; TSSOP24
P2, P3, P4: 53048-0410
R59, R60, R61, R62, R63, R64, R65, R66, R67: 1k; R0805
U9, U10, U11: DISPLAY-OLED-128X32

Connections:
+3V3: C41.1, IC1.24 (VCC), P2.2, P3.2, P4.2, R59.2, R60.2, R61.2, R62.2, R63.2, R64.2, R65.2, R66.2, R67.2, U9.2 (VCC), U10.2 (VCC), U11.2 (VCC); also elsewhere on the board
GND: C41.2, IC1.12 (GND), IC1.21 (A2), P2.1, P3.1, P4.1, U9.1 (GND), U10.1 (GND), U11.1 (GND); also elsewhere on the board
I2C_1_SCL: IC1.22 (SCL), R67.1; also elsewhere on the board
I2C_1_SDA: IC1.23 (SDA), R66.1; also elsewhere on the board
I2C_MUX_0: IC1.1 (A0); also elsewhere on the board
I2C_MUX_1: IC1.2 (A1); also elsewhere on the board
I2C_RESET: IC1.3 (RESET), R65.1; also elsewhere on the board
SCL_OLED1: IC1.5 (SC0), P4.3, R60.1, U11.3 (SCL)
SCL_OLED2: IC1.7 (SC1), P3.3, R62.1, U10.3 (SCL)
SCL_OLED3: IC1.9 (SC2), P2.3, R64.1, U9.3 (SCL)
SDA_OLED1: IC1.4 (SD0), P4.4, R59.1, U11.4 (SDA)
SDA_OLED2: IC1.6 (SD1), P3.4, R61.1, U10.4 (SDA)
SDA_OLED3: IC1.8 (SD2), P2.4, R63.1, U9.4 (SDA)

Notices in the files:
parts and their libraries:
Eagle_STEP-DOWN-CONVERTER: Copyright: Würth Elektronik
diy-modules: Released under the Creative Commons Attribution 4.0 International License: http://creativecommons.org/licenses/by/4.0
con-molex-picoblade: Copyright (C) 2010, Bob Starr
